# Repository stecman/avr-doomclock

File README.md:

# Tiny GPS Clock

This is a `hh:mm:ss` clock that runs from the time contained in NMEA RMC sentences.
The code is targeted at an Atmel ATTiny13A.

Notes:

- As the target microcontroller doesn't have enough RAM to store a full NMEA sentence,
this project uses a custom parser that only reads RMC ("Recommended Minimum") sentences from a UART
and extracts the time from that (see`nmea.c`).

- The ATTiny13A lacks SPI and UART peripherals, so these are implemented in software.

Schematic and construction details can be found on [this project's hackaday.io page](https://hackaday.io/project/163826-gps-wall-clock).

## Building and flashing

The `avr-gcc` toolchain is required to build, but there are no other external dependencies.

```sh
# Build
make

# Flash with programmer configured in Makefile
make flash
```

## Testing

The simple test suite for NMEA RMC sentence decoding can be run manually with:

```sh
make test
```

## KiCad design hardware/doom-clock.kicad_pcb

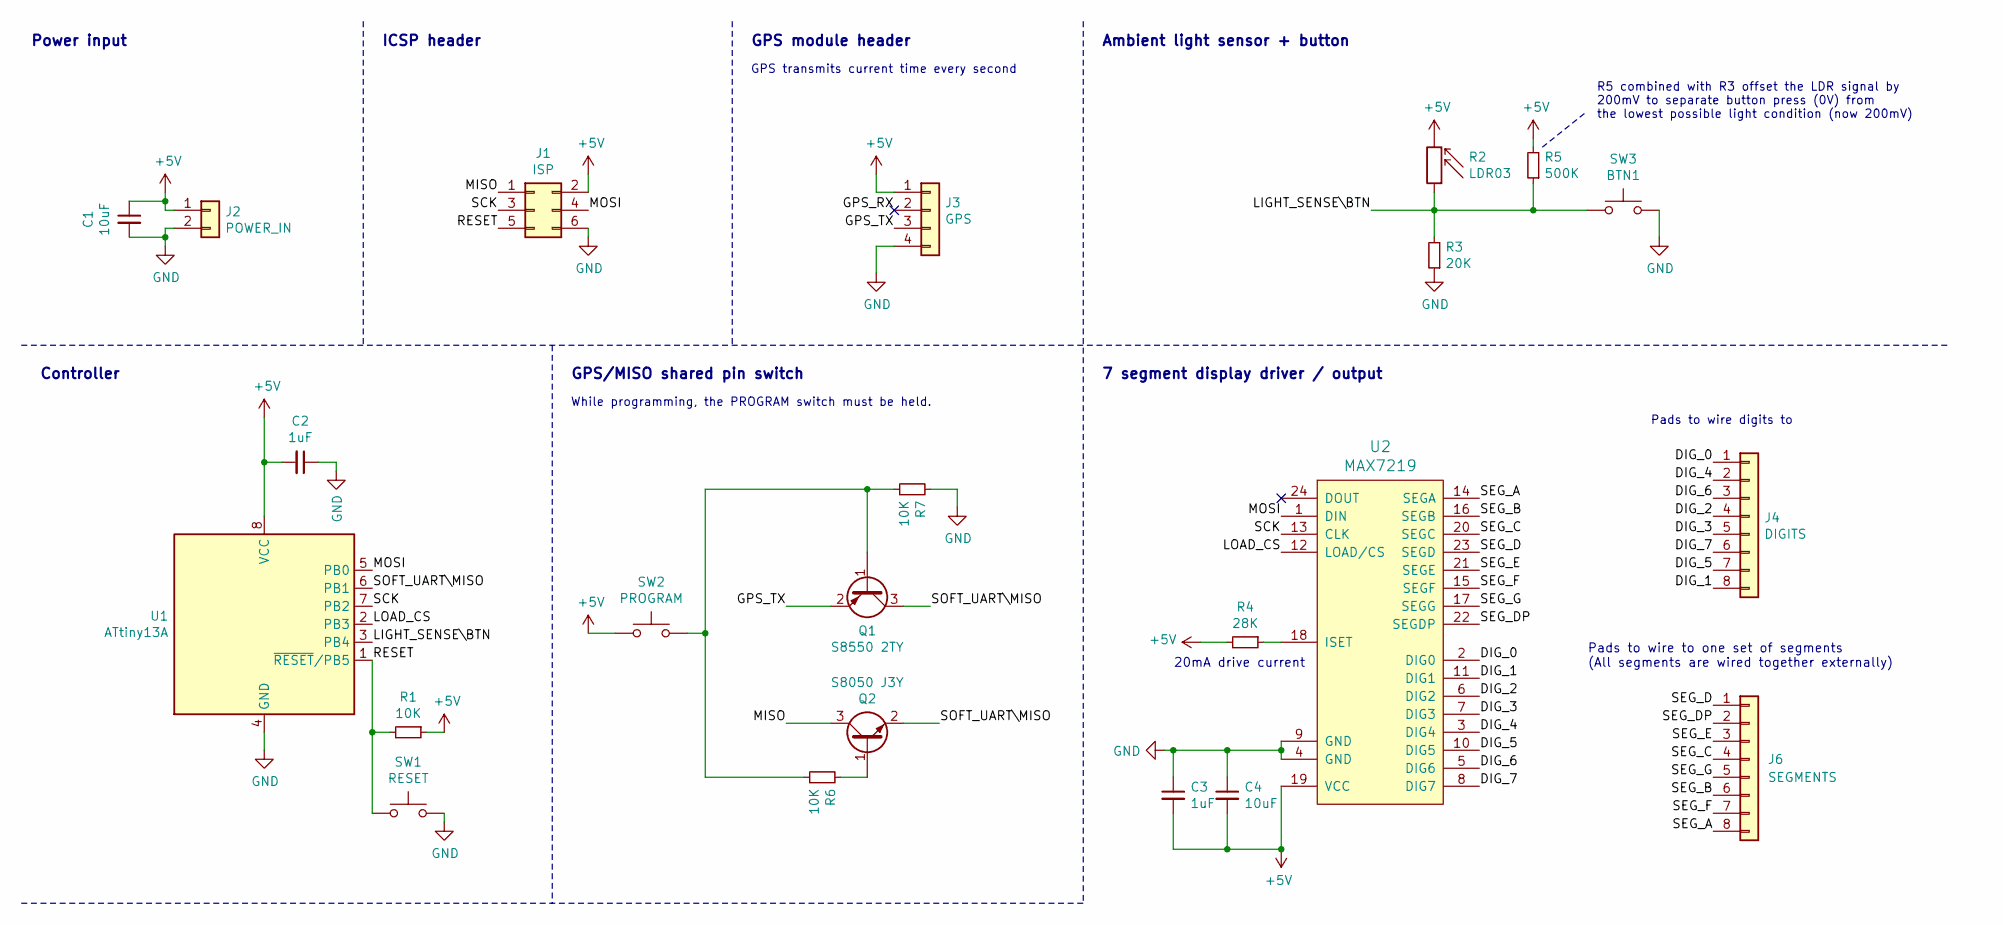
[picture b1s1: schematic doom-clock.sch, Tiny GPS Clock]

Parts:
C1, C4: 10uF; C_1206_3216Metric_Pad1.42x1.75mm_HandSolder
C2, C3: 1uF; C_1206_3216Metric_Pad1.42x1.75mm_HandSolder
J1: ISP; PinSocket_1x06_P1.27mm_Vertical
J2: POWER_IN; PinHeader_1x02_P2.54mm_Vertical
J3: GPS; PinHeader_1x04_P2.54mm_Vertical
J4: DIGITS; PinHeader_1x08_P2.54mm_Vertical
J6: SEGMENTS; PinSocket_1x08_P2.54mm_Vertical
Q1: S8550 2TY; SOT-23
Q2: S8050 J3Y; SOT-23
R1, R6, R7: 10K; R_1206_3216Metric_Pad1.42x1.75mm_HandSolder
R2: LDR03; R_LDR_5.2x5.2mm_P3.5mm_Horizontal
R3: 20K; R_1206_3216Metric_Pad1.42x1.75mm_HandSolder
R4: 28K; R_1206_3216Metric_Pad1.42x1.75mm_HandSolder
R5: 500K; R_1206_3216Metric_Pad1.42x1.75mm_HandSolder
SW1: RESET; SW_SPST_FSMSM
SW2: PROGRAM; SW_SPST_FSMSM
SW3: BTN1; SW_SPST_FSMSM
U1: ATtiny13A; SOIJ-8_SOIC-8
U2: MAX7219; SOP-24

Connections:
+5V: C1.1, C2.2, C3.2, C4.2, J1.2, J2.1, J3.1, R1.1, R2.2, R4.2, R5.2, SW2.1, U1.8 (VCC), U2.19 (VCC)
/DIG_0: J4.1, U2.2 (DIG0)
/DIG_1: J4.8, U2.11 (DIG1)
/DIG_2: J4.4, U2.6 (DIG2)
/DIG_3: J4.5, U2.7 (DIG3)
/DIG_4: J4.2, U2.3 (DIG4)
/DIG_5: J4.7, U2.10 (DIG5)
/DIG_6: J4.3, U2.5 (DIG6)
/DIG_7: J4.6, U2.8 (DIG7)
/GPS_TX: J3.3, Q1.2 (E)
/LIGHT_SENSE\BTN: R2.1, R3.2, R5.1, SW3.1, U1.3 (PB4)
/LOAD_CS: U1.2 (PB3), U2.12 (LOAD/CS)
/MISO: J1.1, Q2.3 (C)
/MOSI: J1.4, U1.5 (PB0), U2.1 (DIN)
/RESET: J1.5, R1.2, SW1.1, U1.1 (~RESET~/PB5)
/SCK: J1.3, U1.7 (PB2), U2.13 (CLK)
/SEG_A: J6.8, U2.14 (SEGA)
/SEG_B: J6.6, U2.16 (SEGB)
/SEG_C: J6.4, U2.20 (SEGC)
/SEG_D: J6.1, U2.23 (SEGD)
/SEG_DP: J6.2, U2.22 (SEGDP)
/SEG_E: J6.3, U2.21 (SEGE)
/SEG_F: J6.7, U2.15 (SEGF)
/SEG_G: J6.5, U2.17 (SEGG)
/SOFT_UART\MISO: Q1.3 (C), Q2.2 (E), U1.6 (PB1)
GND: C1.2, C2.1, C3.1, C4.1, J1.6, J2.2, J3.4, R3.1, R7.2, SW1.2, SW3.2, U1.4 (GND), U2.4 (GND), U2.9 (GND)
unnamed: Q1.1 (B), R6.1, R7.1, SW2.2
unnamed: Q2.1 (B), R6.2
unnamed: R4.1, U2.18 (ISET)

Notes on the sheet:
20mA drive current
Pads to wire to one set of segments (All segments are wired together externally)
Power input
ICSP header
Controller
GPS module header
GPS/MISO shared pin switch
Ambient light sensor + button
7 segment display driver / output
R5 combined with R3 offset the LDR signal by 200mV to separate button press (0V) from the lowest possible light condition (now 200mV)
While programming, the PROGRAM switch must be held.
GPS transmits current time every second
Pads to wire digits to

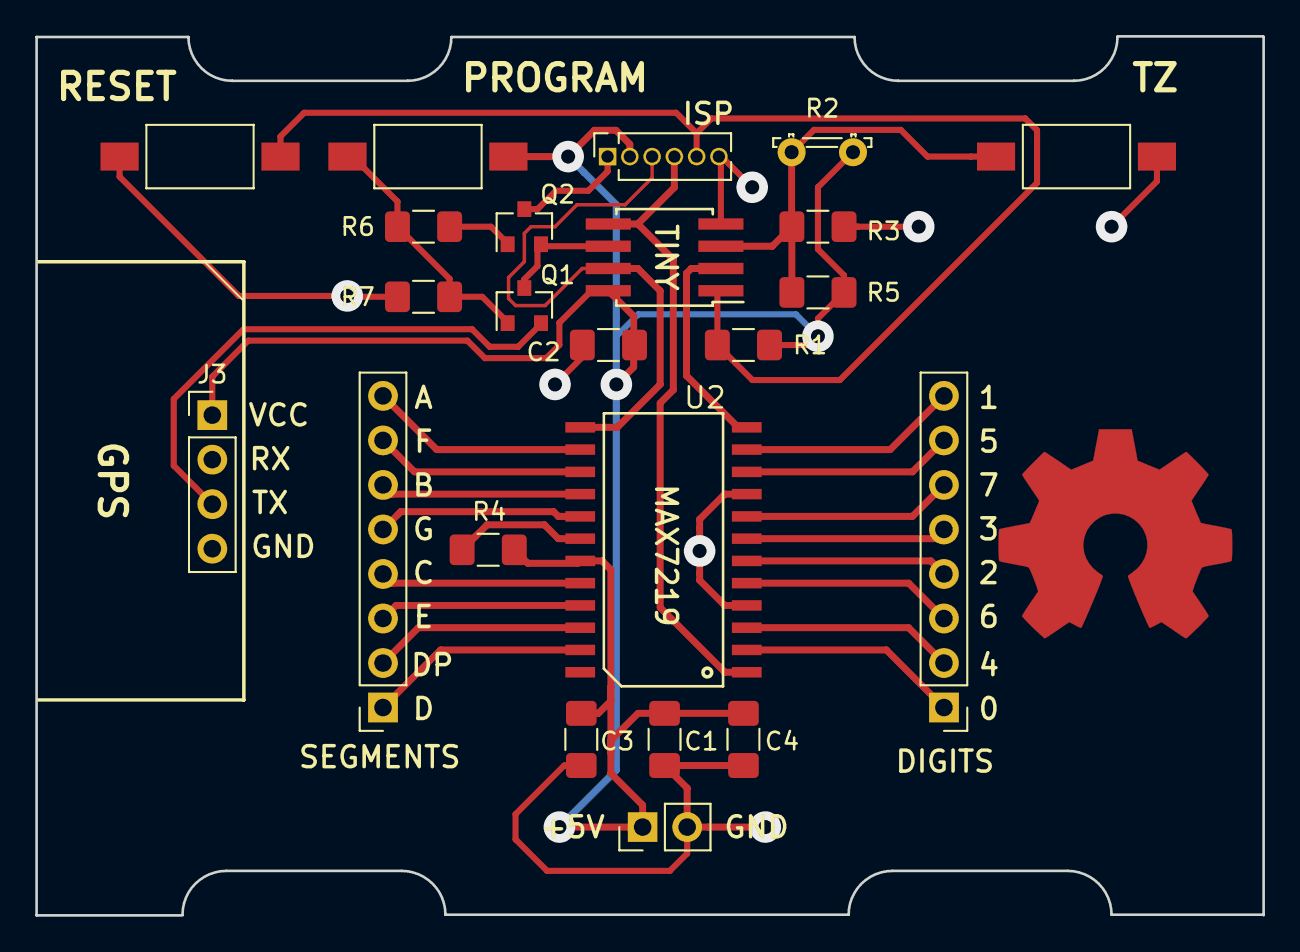
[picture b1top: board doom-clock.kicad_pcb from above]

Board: 2 copper layers, 70.0 x 50.1 mm, 23 parts (0 on the bottom side), 29 nets.

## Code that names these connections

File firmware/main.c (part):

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#include "softuart.c"
#include "nmea.c"

#define PIN_MOSI PB0
#define PIN_SCK PB2
#define PIN_LOAD PB3
#define PIN_LIGHT_SENSE PB4

#define EEPROM_TIMEZONE_ADDR 0
#define kNumDigits 6
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
static inline void setup_adc()
{
    // Select PB4 (PIN_LIGHT_SENSE) in the ADC multiplexer
    // Put the significant 8-bits in the upper register as we only want to read that
    ADMUX = _BV(MUX1) | _BV(ADLAR);

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{
    // Re-purpose an unused register for single instruction set/clear
    // The reset pin isn't used as I/O, so this changing its registers has no effect
    DDRB |= _BV(PB5);
}

static inline uint8_t is_display_pending()
{
    // See set_display_pending_flag for what's going on here
    return DDRB & _BV(PB5);
}

static inline void clear_display_pending_flag()
{
    // See set_display_pending_flag for what's going on here
    DDRB &= ~_BV(PB5);
}


static inline void set_timepulse_seen_flag()
{
    // Re-purpose an unused register for single instruction set/clear
    // This "input buffer disable register" bit isn't functional as PB0 is always an output
    DIDR0 |= _BV(AIN0D);
}

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
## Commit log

2019-02-04 Initial implementation with displayed time read from serial GPS
2019-02-04 Added basic readme and licence
2019-02-04 Fix digit decoding (late-night off math error)
    The display was counting to 11 instead of 10 ...37, 38, 39, 3-, 41, 42...
2019-02-10 Fix wait indicator not wrapping at digit count
2019-02-12 Add automatic display brightness based on ambient light level
    This adds code to read the LDR and set brightness smoothly. This may be completely
    overkill, but I'll see how it performs with real use. The problem could be solved
    with less program space using a single threshold with hysteresis to switch between
    "day" and "night" modes.
    I suspect flickering brightness might be an issue with this, which means it would
    need hysteresis anyway. With this chnage the code is now 966 bytes, so something
2019-02-12 Make small optimisations to free a little program space
    This change-set takes the program size from 966 bytes to 920 bytes, freeing up
    just 4.4% of the total program space.
    - hex2int doesn't need to deal with lowercase characters. Forcing this loop
    to unroll saves 10 bytes. Clarified the code a little here too.
    - Removed null terminator from GPRMC string as it's not used (saves 2 bytes)
    - Removed initial brightness setting from max7219_init (saves 6 bytes):
2019-02-12 Remove committed test binary
2019-02-12 Reduce compiled size of uart_read_byte function by 18 bytes
    - Half-bit delay is now 49uS as this generates a fewer instructions for the
    configured clock frequency (no padding with nops)
    - Packed stopbit delay into loop to avoid two inlined _delay_us calls.
    This makes the size of this routine on-par with AVR ASM implementations
    I've seen around.
2019-02-19 Improve the test output to abort on failure and use fancy colours
    This also adds a requirement for the tests to run successfully before the
    code will be flashed to a device.
    I really didn't need to do this, but it was a bit of fun.
2019-02-19 Update readme with Hackaday project page link
2019-04-01 Drop -mcall-prologues gcc option to save 42 bytes
    This codebase doesn't benefit from this option that's in my default
    avr-gcc makefile. Removing it saves a bunch of space at the moment.
2019-04-07 Add crude ability to set timezone
    This hasn't had much thought put into it - daylight saving time ended here
    today and I just needed to make the clock show the right time.
2019-05-09 Remove explicit inline keywords where not needed
    Most of this will be inlined by the compiler if needed. Leaving inline
    keywords only where it's explicitly actually wanted.
2019-05-09 Fix negative timezone not handled correctly during display
    DateTime.hour is unsigned, so a negative timezone was displaying
    60-something instead of the correct adjusted hour.
2019-05-09 Try to avoid timezone changing occassionally without button press
    The timezone has skipped forward 1-2 hours a few times in the last month.
    Something (maybe power glitches while it's already very dark) is causing
    the ADC reading to drop below the button-press threshold for one reading,
    which is advancing the timezone.
    This changes the logic to advance the timezone at the end of the 500ms
    period, requiring 5 readings 100ms apart to register as button presses.
2020-02-15 Reduce code size by 44 bytes to make room for timezone saving code
    This takes the compiled binary size from 994 to 950 bytes in preparation
    for adding code to persist the selected timezone in eeprom.
    Changes in order of most to least space saving:
    - Consolidated display clearing into a single function to save 30 bytes.
    Clearing was performed selectively in few different places which wasted
    quite a bit of code space. The refactored code ended up simpler as a bonus.
2020-02-15 Store the last used timezone in eeprom and restore during power-on
    It's been bothering me that the clock doesn't remember its timezone as
    I've needed to unplug it a few times recently. I'm reluctant to unplug
    it currently as I need to take the clock off the wall each time to set
    the timezone again.
2020-02-15 Move time mutation out of display_update() for grok-ability
    Coming back to this code after 9 months, I was irked by the display_update()
    mutating the time each call. This isn't technically a problem as the
    function is only called once after reading the time from the GPS, but
    it seems clearer to separate the application of timezone offset to the
    updating of digits on the display.
    This change doesn't affect binary size.
2020-02-15 Fix timezone restored from eeprom typed as unsigned with bad comparison logic
    Fixes dumb late-night mistakes in the implementation
2020-02-15 Free up an additional 8 bytes for saved timezone validation fix. This brings the code size from 1032 bytes in the previous commit to 1024 bytes (exactly 100% flash usage).
2020-09-18 Add Kicad schematic and layout
    I'd recommend not using the layout included here as it's pretty gross.
    Best to create your own layout from the schematic.
2021-03-20 Add additional test for expected no signal case
2021-03-20 Remove redundant multiplication from manually unrolled loop
    This doesn't change the code size as GCC was smart enough to drop the
    redundant multiplication. Tidying this up for human readers in any case.
2021-03-20 Tidy up logic for checksum field parsing
    This is only intended to improve readability. No change to code size
2021-03-20 Remove unecessary exclusive else condition in spi_send
    This saves 4 bytes by always clearing the MOSI output instead of
    conditionally if the bit is not set. While the SCLK line is low,
    though this will result in extra pulses on the MOSI line that weren't
    there before.
2021-07-17 Squeeze an additional 48 bytes of program space out of the existing code
    - Use a custom start-up implementation to remove redundant start-up code
    added by GCC to accommodate software resets (which never happen), free
    up space that was given to unused interrupt vectors. Also removes a few
    instructions related to the program exiting as this can't happen.
    This frees up 24 bytes for other code.
    - Combine MAX7219 command and data into a 16-bit value to be clocked out
2021-07-17 Change fuses to include EESAVE to preserve eeprom across flashing
2021-07-17 Change constants to defines to avoid warnings about losing const-ness
2021-07-17 Reduce delay length and increase repetitions to save 6 bytes
    The implementation of _delay_ms is slightly smaller at 25ms than 100ms.
    Since we're already looping around this, some program space can be saved
    while keeping the delay to the user the same
2021-07-18 Replace AVR eeprom read/write functions to save 36 bytes program space
    This uses the EEPROM read and write implementations from the datasheet,
    but strips out waits for the previous write to complete. This check isn't
    needed as our reads only occur on start-up, and writes are at least a
    few seconds apart due to the way the timezone changing UI works.
    Defining these statically lets the compiler optimise further as these
    functions are only called once each.
2021-07-18 Compile as a single unit to maximise compiler optimisation opportunities
    This saves 84 bytes in the current code at the cost of making the compiled
    assembly harder to follow as 85% of the program becomes a single function.
    Since space saving is the name of the game, this is a worthwhile compromise.
    Introduces a define AVRSTATIC so functions can be made static when
    compiling the firmware, and left as `auto` when compiling the test
    cases. If this ends up being annoying or confusing, the test cases can
2021-07-18 Fix display intensity wrapping to 0x10 instead of maxing out at 0x0F
    The display brightness value was able to go to 16, which was interpreted
    by the MAX7219 as the lowest brightness (as it only looks at the low nibble).
    Fix this so it can go brighter than the number of brightness table entries.
    This didn't occur during normal use. I only noticed this when shining a
    bright light directly at the LDR while testing.
2021-07-20 Buffer display values ready for output on timepulse signal
    This implements a display buffer, but is still a work in progress
2021-07-20 Jump to main() instead of calling, as it doesn't need to be on the stack
    Main will never return, so it's a waste of RAM pushing the return address
    to the stack.
2021-07-20 Wait until timepulse OR uart receive instead of only timepulse
    Timepulse isn't generated if the GPS doesn't have a match (by default -
    we probably don't have enough space to send config options). This effectively
    locks up the clock until a GPS fix is made
2021-07-21 Fix zero register not being zero as GCC expects
    This breaks a lot of logic!
2021-07-26 Fix display_clear() not clearing first digit (regression)
2021-07-26 Fall back to displaying time as read while timepulse signal isn't firing
    Out of the box, the GPS module only generates a timepulse signal when it
    has a fix. We still want to display time in this state, but indicate that
    the display isn't synced to the timepulse.
    - Updated the main loop to detect if a timepulse is occurring and display
    the time accordingly.
    - Made the last decimal point illuminate if timepulse isn't being received.
